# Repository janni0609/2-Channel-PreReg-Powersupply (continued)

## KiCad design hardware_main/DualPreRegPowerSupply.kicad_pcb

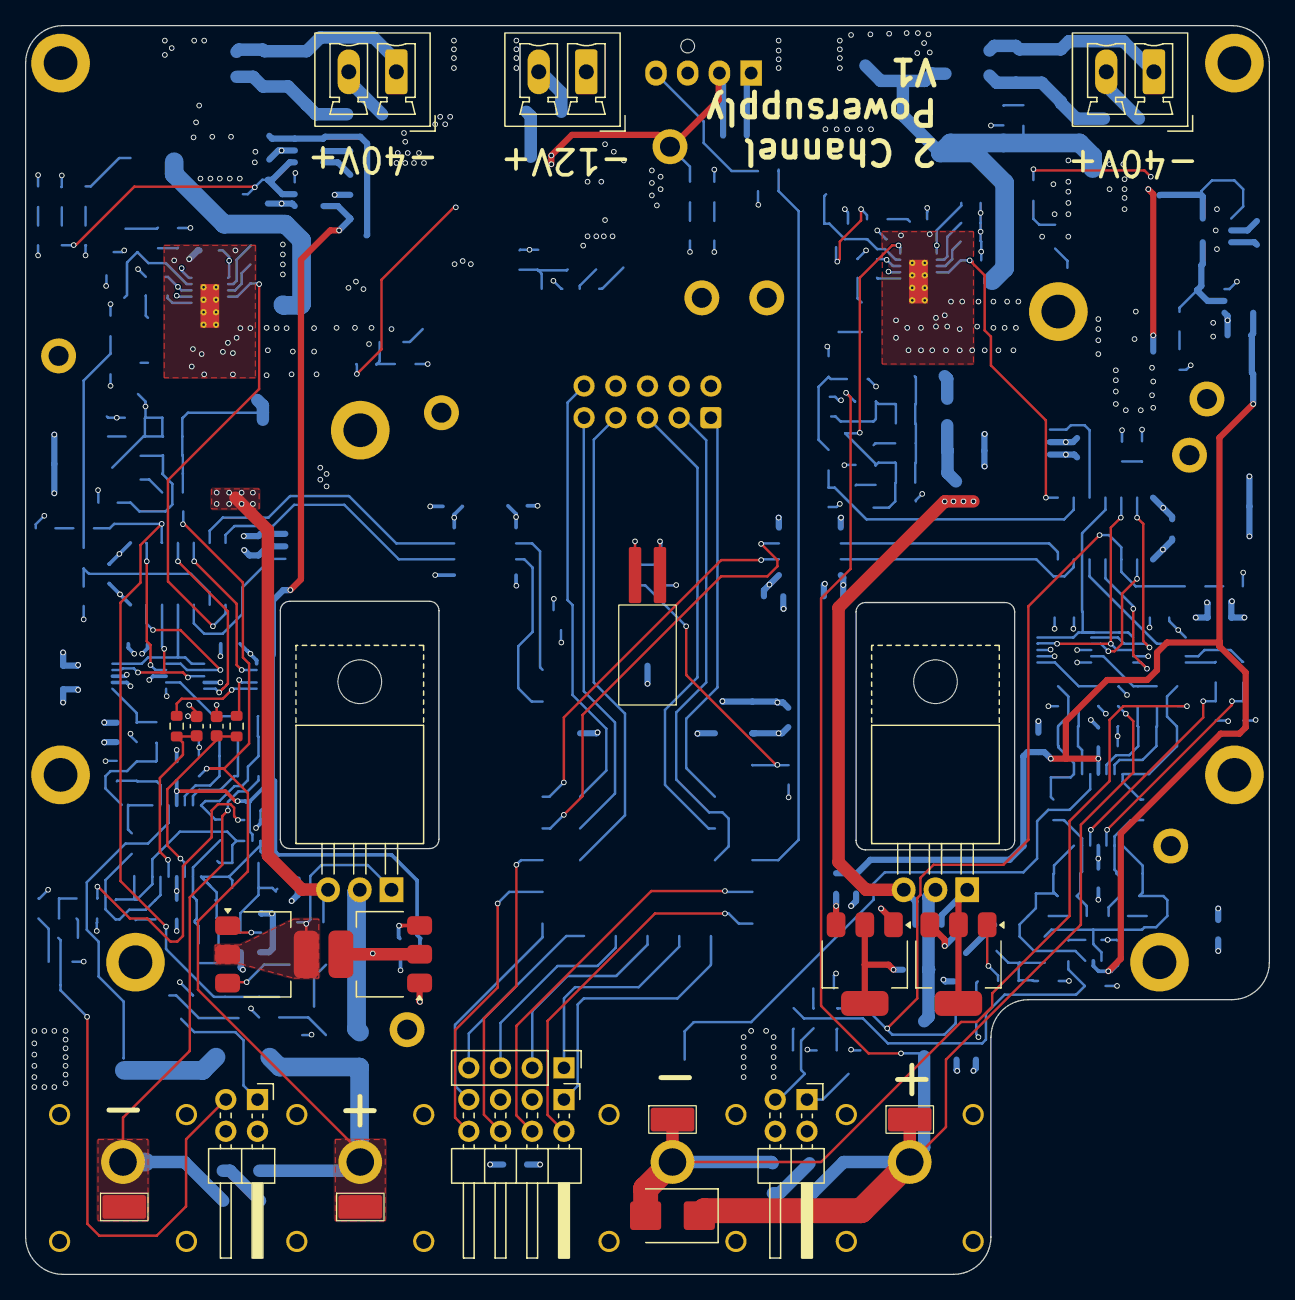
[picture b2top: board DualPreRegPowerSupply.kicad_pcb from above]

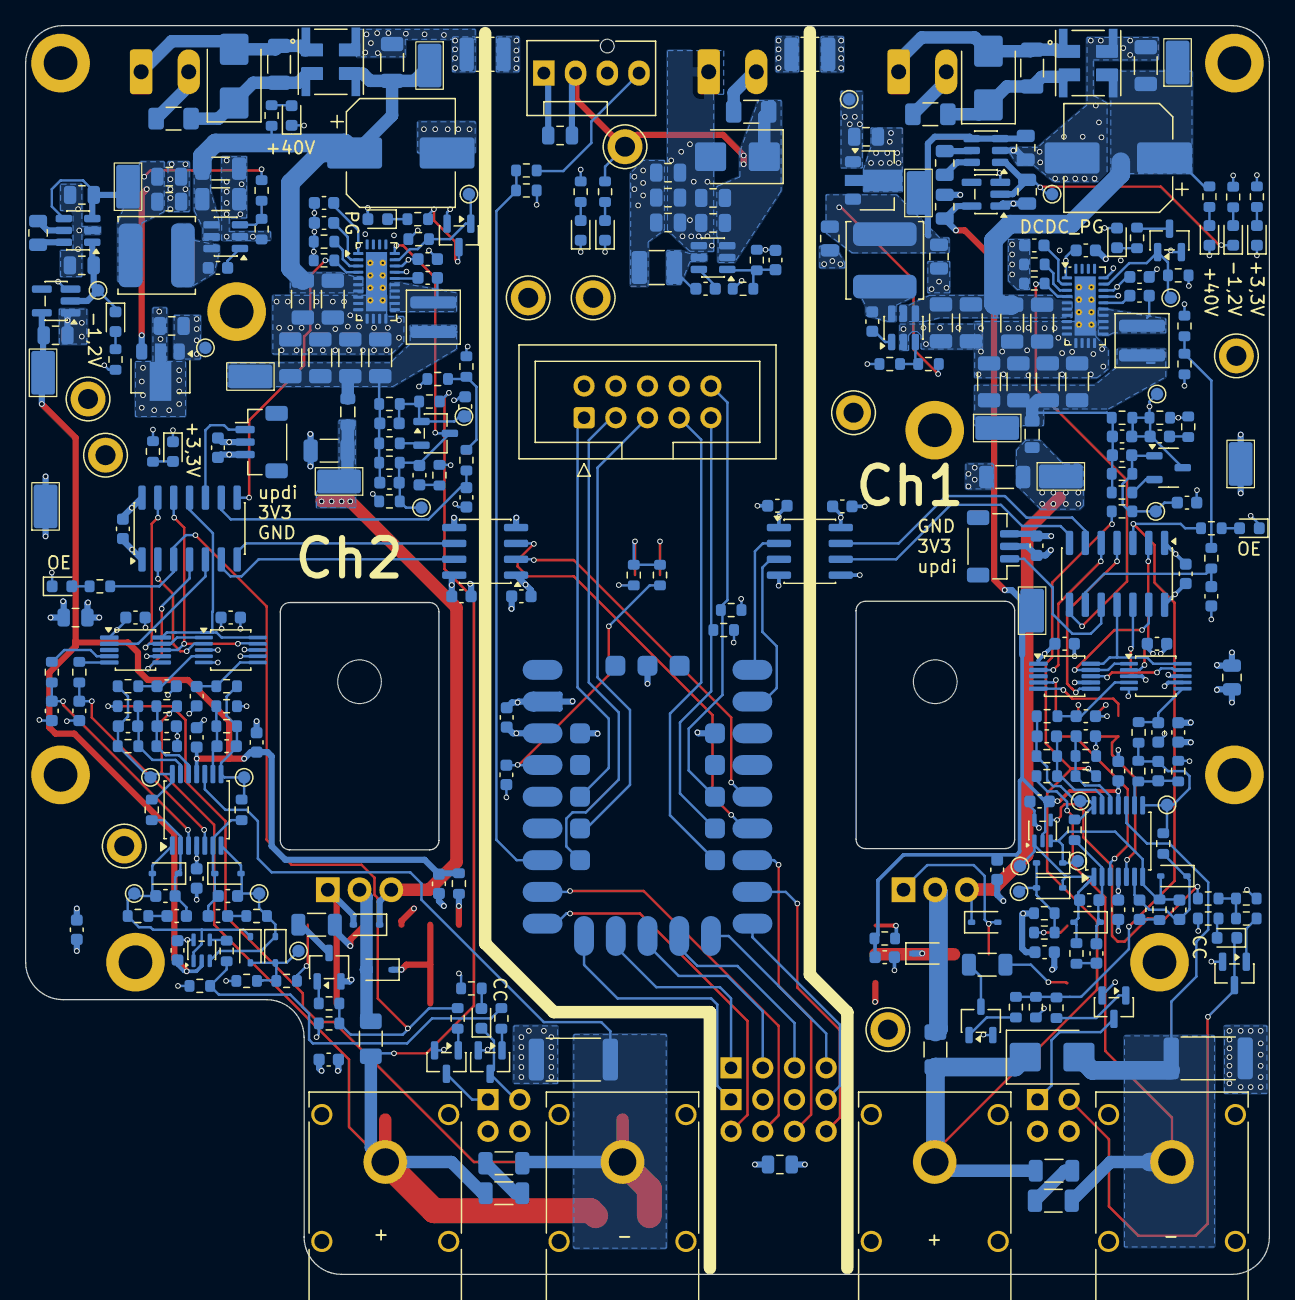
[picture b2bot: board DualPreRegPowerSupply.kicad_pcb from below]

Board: 4 copper layers, 99.6 x 100.0 mm, 379 parts (350 on the bottom side), 195 nets.

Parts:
A401: Waveshare RP2350-Tiny; Waveshare_PR2350_tiny
C101, C102, C105, C107, C120, C135, C136, C140, C141, C143, C145, C201, C309, C405, C501, C502, C509, C511, C512, C513, C601, C603, C1001, C1002: 10u; C_1206_3216Metric
C103, C104, C106, C108, C109, C115, C117, C118, C126, C128, C132, C144, C147, C301, C302, C307, C310, C402, C503, C505, C703, C704, C801, C802, C803, C805, C806, C903, C1003, C1015, C1205, C1301: 100n; C_0603_1608Metric
C110, C122, C123, C203, C504, C507, C804: 1u; C_0603_1608Metric
C111, C303: 47n; C_0603_1608Metric
C112, C304, C807, C1302: 27n; C_0603_1608Metric
C113, C114, C701, C702: 4,7u; C_0603_1608Metric
C119, C137, C506, C510, C908, C1401: opt; C_0603_1608Metric
C121, C130, C134, C305, C306, C308: 10p; C_0603_1608Metric
C124, C131, C905, C906, C907, C1005, C1007: 22u; C_0805_2012Metric
C125, C602: CHV1210N1K0103KXT; C_1210_3225Metric
C127, C139, C142, C146, C202, C404, C808, C901, C902, C1006, C1009, C1010, C1011, C1303: 10u; C_0805_2012Metric
C129, C508: 1n; C_0603_1608Metric
C133, C1008: 1u; C_0805_2012Metric
C138, C604: 100u; CP_Elec_8x10.5
C904, C1004, C1203: 100p; C_0603_1608Metric
C1012, C1013, C1201, C1202: 2,2u; C_0603_1608Metric
C1014, C1204: 22p; C_0603_1608Metric
D101, D601: SMBJ40A; D_SMB
D103, D107, D801, D802: red LED 3V3; LED_0603_1608Metric
D104, D602: green LED 40V; LED_0603_1608Metric
D105, D903, D1001: green LED 3V3; LED_0603_1608Metric
D106, D1002: green LED -5V; LED_0603_1608Metric
D201, D401: SMBJ36A; D_SMB
D901: SMBJ12A; D_SMB
D902: green LED 12V; LED_0603_1608Metric
D904, D1401: green LED PG; LED_0603_1608Metric
D1003, D1004, D1006, D1007, D1008, D1201, D1202, D1204, D1205, D1206: 1N4148WS; D_SOD-323
D1005, D1203: MM3Z4V7T1G; D_SOD-323
F101, F601, F901: 3,5A; Fuse_1206_3216Metric
F102, F301: 3A; Fuse_1206_3216Metric
FL101, FL601: DLW5BTM102TQ2L; L_CommonModeChoke_Murata_DLW5BTMxxxSQ2x_5x5mm
H101, H102, H103, H104, H201, H202, H401, H402: M2,5; MountingHole_2.7mm_M2.5_DIN965_Pad
J101, J601, J901: Power Input; PhoenixContact_MCV_1,5_2-G-3.81_1x02_P3.81mm_Vertical
J102, J801: Conn_01x03_Pin; JST_SH_BM03B-SRSS-TB_1x03-1MP_P1.00mm_Vertical
J103, J802: Conn_02x02_Odd_Even; PinHeader_2x02_P2.54mm_Horizontal
J201, J402: Banana_Red; Banana_Cliff_FCR7350R_S16N-PC_Horizontal
J202, J403: Banana_Black; Banana_Cliff_FCR7350B_S16N-PC_Horizontal
J203: Conn_02x04_Odd_Even; PinHeader_2x04_P2.54mm_Horizontal
J204: Conn_02x05_Odd_Even; IDC-Header_2x05_P2.54mm_Vertical
J205: Conn_01x04_Pin; PinHeader_1x04_P2.54mm_Vertical
L101, L1001: 33u VLS6045EX-330M; L_TDK_VLS6045EX_VLS6045AF
L102, L501: 10u 74438357100; L_Wuerth_MAPI-4030
L201, L401: 1u; L_0805_2012Metric
L901: 6,8u LBC3225T6R8MR; L_1210_3225Metric
M401: Fan_4pin; FanPinHeader_1x04_P2.54mm_Vertical
Q101, Q501: MMBT3906; SOT-23-3
Q102, Q107, Q301, Q304: BCP56; SOT-223
Q103, Q302: BSS138; SOT-23-3
Q104, Q303: TIP125; TO-220-3_Horizontal_TabUp
Q105, Q106, Q801, Q802, Q901, Q1401: BSS138; SOT-23
R101, R102, R103, R109, R113, R120, R201, R202, R203, R204, R205, R301, R302, R310, R501, R801, R802, R808, R906, R1302, R1402: 10k; R_0603_1608Metric
R104, R105, R118, R125, R135, R137, R308, R404, R506, R701, R702, R804, R805: 1k; R_0603_1608Metric
R106, R303: 18k; R_0603_1608Metric
R107, R121, R304, R311: 0; R_0603_1608Metric
R108, R502: 60,4k; R_0603_1608Metric
R110, R122, R503, R505: opt; R_0603_1608Metric
R112, R305: 1,2k; R_0603_1608Metric
R114, R1001: 75k; R_0603_1608Metric
R115, R1002: 16,2k; R_0603_1608Metric
R116, R119, R306, R309: 2,2k 0,1%; R_0603_1608Metric
R117, R307: 3,3k; R_0603_1608Metric
R123, R312: 220; R_0603_1608Metric
R124, R136, R140, R803, R806, R905, R1003, R1401: 2,4k; R_0603_1608Metric
R126, R507: 4,99k; R_0603_1608Metric
R127, R128, R313, R314: 33k 0,1%; R_0603_1608Metric
R129, R315: 150; R_1206_3216Metric
R130, R508, R903: 62k; R_0603_1608Metric
R131, R316: 11k 0,1%; R_0603_1608Metric
R132, R317: 1k 0,1%; R_0603_1608Metric
R133, R509: 100k; R_0603_1608Metric
R134, R601: 38k; R_0603_1608Metric
R138, R318: 100m; R_2512_6332Metric
R139, R901, R904, R1004: ###; R_0603_1608Metric
R141, R319: 200m; R_1206_3216Metric
R142, R320: 47; R_0603_1608Metric
R807, R1301: 12k; R_0603_1608Metric
R902: 196k; R_0603_1608Metric
TH101, TH801: NCU18XH103F60RB; R_0603_1608Metric
TH201: Thermistor_NTC; Flex NTC
TP101, TP301: Vsense; TestPoint_Pad_D1.0mm
TP102, TP302: CV_loop; TestPoint_Pad_D1.0mm
TP103, TP303: CC_loop; TestPoint_Pad_D1.0mm
TP104, TP304: CC/CV; TestPoint_Pad_D1.0mm
TP105, TP305: Isense; TestPoint_Pad_D1.0mm
TP106, TP107, TP110, TP501, TP502, TP503, TP608, TP901, TP1401, TP1506: TestPoint_Alt; TestPoint_Pad_D1.0mm
TP108, TP112, TP201, TP202, TP203, TP401, TP402, TP403, TP505, TP601, TP605, TP606, TP607, TP1503, TP1504, TP1505: TestPoint; SMD Test Point PCWCTE
TP306, TP307, TP308, TP602, TP603, TP604, TP1501, TP1502, TP1507: TestPoint_Alt; TestPoint_Keystone_5005-5009_Compact
U101, U301: TLV4387PWR; TSSOP-14_4.4x5mm_P0.65mm
U102, U801: ISO6721RFBD; SOIC-8_3.9x4.9mm_P1.27mm
U104, U501: LT8612; QFN-28-1EP_3x6mm_P0.5mm_EP1.7x4.75mm_ThermalVias
U105, U302: LMV331; SOT-353_SC-70-5
U106, U802: ATtiny1614-SS; SOIC-14_3.9x8.7mm_P1.27mm
U107, U701: ADS1118IDGS; TSSOP-10_3x3mm_P0.5mm
U108, U702: MCP48FVB22; MSOP-10_3x3mm_P0.5mm
U109, U1002: AP7383; SOT-89-3
U110, U1003: LM2776; SOT-23-6
U111, U1004: XC6901D121MR-G; SC-74A-5_1.55x2.9mm_P0.95mm
U601, U1501: LMR51606; SOT-23-6
U901: AP63200WU; TSOT-23-6

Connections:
+3.3V: A401.30 (3V3), A401.35 (3V3), C106.1, C202.1, C402.1, C801.1, C904.1, C905.1, C906.1, C907.1, J203.3, J204.8, L901.2, R201.2, R203.2, R204.2, R902.1, R904.1, TP307.1 (1_1), U102.1 (VCC1), U801.1 (VCC1)
+3V3Ch1: C301.1, C307.1, C507.1, C703.1, C704.1, C802.1, C803.1, C805.1, C808.1, C1009.1, C1012.1, C1015.1, D904.2 (A), J801.2, J802.2, J802.4, R307.1, R308.1, R801.1, R806.1, R906.1, R1003.1, TP501.1 (1_1), TP602.1 (1_1), TP606.1 (1_1), U301.4 (V+), U302.5 (V+), U501.22 (BIAS), U701.8 (VDD), U702.1 (Vdd), U801.8 (VCC2), U802.1 (VCC), U1002.1 (VO), U1004.3 (CE)
+3V3Ch2: C103.1, C109.1, C117.1, C123.1, C126.1, C128.1, C132.1, C139.1, C144.1, C1201.1, C1205.1, C1303.1, D1401.2 (A), J102.2, J103.2, J103.4, R109.1, R117.1, R118.1, R136.1, R140.1, R1402.1, TP106.1 (1_1), TP1504.1 (1_1), TP1507.1 (1_1), U101.4 (V+), U102.8 (VCC2), U104.22 (BIAS), U105.5 (V+), U106.1 (VCC), U107.8 (VDD), U108.1 (Vdd), U109.1 (VO), U111.3 (CE)
+12V: C404.1, C901.1, C902.1, D901.1 (A1), F901.2, M401.2 (+), R901.1, TP308.1 (1_1), U901.2 (EN), U901.3 (IN)
+40VCh1: C501.1, C502.1, C603.1, C604.1, C1001.1, C1002.1, FL601.3, R601.1, TP601.1 (1_1), U501.5 (Vin), U501.6 (Vin), U501.7 (Vin), U601.4 (EN), U601.5 (VIN)
+40VCh2: C101.1, C102.1, C105.1, C107.1, C135.1, C138.1, FL101.3, R134.1, TP108.1 (1_1), U104.5 (Vin), U104.6 (Vin), U104.7 (Vin), U1501.4 (EN), U1501.5 (VIN)
-1V2Ch1: C302.2, C307.2, C310.2, C1011.2, C1013.2, R320.2, TP607.1 (1_1), U301.11 (V-), U302.2 (V-), U1004.5 (VOUT)
-1V2Ch2: C104.2, C132.2, C146.2, C147.2, C1202.2, R142.2, TP1505.1 (1_1), U101.11 (V-), U105.2 (V-), U111.5 (VOUT)
/Ch1Power1/DAC_ADC/DAC_LAT: U106.4 (PA6), U108.6 (LAT/HVC)
/Ch1Power1/DAC_ADC/Isense: C134.1, R103.1, R105.2, R131.1, TP105.1 (1_1), U101.8
/Ch1Power1/DAC_ADC/Iset: C1302.1, R1302.1, U101.5 (+)
/Ch1Power1/DAC_ADC/SPI_ADC_CS: U106.2 (PA4), U107.2 (~CS)
/Ch1Power1/DAC_ADC/SPI_DAC_CS: U106.5 (PA7), U108.2 (~CS)
/Ch1Power1/DAC_ADC/SPI_MISO: U106.12 (PA2), U107.9 (DOUT/~DRDY), U108.8 (SDO)
/Ch1Power1/DAC_ADC/SPI_MOSI: U106.11 (PA1), U107.10 (DIN), U108.10 (SDI)
/Ch1Power1/DAC_ADC/SPI_SCK: U106.13 (PA3), U107.1 (SCLK), U108.9 (SCK)
/Ch1Power1/DAC_ADC/Vsense: C121.1, R102.1, R104.2, R116.1, TP101.1 (1_1), U101.14
/Ch1Power1/DAC_ADC/Vset: C1301.1, R1301.1, U101.3 (+)
/Ch1Power1/DCDCTracking/BST: C118.1, U104.20 (BST)
/Ch1Power1/DCDCTracking/DCDC_FB: C119.1, C129.1, Q101.3 (C), R122.1, R126.2, TP107.1 (1_1), U104.24 (FB)
/Ch1Power1/DCDCTracking/Enable: R101.2, U104.4 (EN/UV), U106.8 (PB1)
/Ch1Power1/DCDCTracking/PG: Q1401.1 (G), R1402.2, TP1401.1 (1_1), U104.23 (PG)
/Ch1Power1/DCDCTracking/SW: C118.2, L102.1, U104.15 (SW), U104.16 (SW), U104.17 (SW), U104.18 (SW), U104.19 (SW)
/Ch1Power1/DCDCTracking/SW_OUT: C129.2, C136.1, C137.1, C140.1, C141.1, C143.1, L102.2, L401.1, R122.2, R125.2, R130.2, TP112.1 (1_1)
/Ch1Power1/Input/Input+: F101.1, J101.2
/Ch1Power1/Input/Input-: C120.2, D101.2 (A2), FL101.1, J101.1
/Ch1Power1/Input/Input_Fused+: C120.1, D101.1 (A1), F101.2, FL101.2
/Ch1Power1/Linear_PostReg/Base: Q102.1 (B), R121.2
/Ch1Power1/Linear_PostReg/Base_drive: D1203.2 (A), Q102.2 (C), Q102.4 (C), Q104.1 (B)
/Ch1Power1/Linear_PostReg/CC_loop: C1203.2, D1201.2 (A), D1205.1 (K), R107.2, TP103.1 (1_1), U101.7, U105.3 (-)
/Ch1Power1/Linear_PostReg/CC/CV_loop: D1205.2 (A), D1206.2 (A), R118.2, R121.1, TP104.1 (1_1)
/Ch1Power1/Linear_PostReg/CC/~CV: R112.2, R117.2, R137.1
/Ch1Power1/Linear_PostReg/CV_loop: C1204.2, D1202.2 (A), D1206.1 (K), R106.2, TP102.1 (1_1), U101.1, U105.1 (+)
/Ch1Power1/Linear_PostReg/OE: R120.2, R123.2, R124.1, R135.1, U106.3 (PA5)
/Ch1Power1/Linear_PostReg/OUT+: D401.1 (A1), F102.2, J402.1 (Pin_1_1), R127.2, R133.2, R141.1, TP402.1 (1_1)
/Ch1Power1/Linear_PostReg/OUT-: C145.2, D401.2 (A2), J403.1 (Pin_1_1), R128.2, R138.1, TP403.1 (1_1), U101.10 (+)
/Ch1Power1/Linear_PostReg/PreReg: C405.1, D1203.1 (K), L401.2, Q104.3 (E), TP401.1 (1_1)
/Ch1Power1/Linear_PostReg/preFuseOut+: D1204.2 (A), F102.1, Q104.2 (C)
/Ch1Power1/MCU/NTC1: C122.1, R113.2, U106.9 (PB0)
/Ch1Power1/MCU/Rx: U102.7 (OUTA), U106.6 (PB3)
/Ch1Power1/MCU/Tx: U102.6 (INB), U106.7 (PB2)
/Ch1Power1/MCU/UPDI: J102.1, U106.10 (~RESET/PA0)
/Ch1Power1/MCU/~LED_CC: D107.1 (K), J103.3, Q106.3 (D)
/Ch1Power1/MCU/~LED_Enable: J103.1, Q105.3 (D)
/Ch1Power1/Power/5V: C124.1, C127.1, C131.1, L101.2, R114.1, TP1503.1 (1_1), U109.3 (VI), U110.3 (VIN), U110.4 (EN)
/Ch1Power1/Power/SW: C115.2, L101.1, U1501.6 (SW)
/Ch1Power1/Rx_Ctr: A401.5 (GPIO5), U102.3 (OUTB)
/Ch1Power1/Tx_Ctr: A401.4 (GPIO4), U102.2 (INA)
/Ch1Power/DAC_ADC/DAC_LAT: U702.6 (LAT/HVC), U802.4 (PA6)
/Ch1Power/DAC_ADC/Isense: C308.1, R302.1, R316.1, R702.2, TP305.1 (1_1), U301.8
/Ch1Power/DAC_ADC/Iset: C807.1, R808.1, U301.5 (+)
/Ch1Power/DAC_ADC/SPI_ADC_CS: U701.2 (~CS), U802.2 (PA4)
/Ch1Power/DAC_ADC/SPI_DAC_CS: U702.2 (~CS), U802.5 (PA7)
/Ch1Power/DAC_ADC/SPI_MISO: U701.9 (DOUT/~DRDY), U702.8 (SDO), U802.12 (PA2)
/Ch1Power/DAC_ADC/SPI_MOSI: U701.10 (DIN), U702.10 (SDI), U802.11 (PA1)
/Ch1Power/DAC_ADC/SPI_SCK: U701.1 (SCLK), U702.9 (SCK), U802.13 (PA3)
/Ch1Power/DAC_ADC/Vsense: C305.1, R301.1, R306.1, R701.2, TP301.1 (1_1), U301.14
/Ch1Power/DAC_ADC/Vset: C806.1, R807.1, U301.3 (+)
/Ch1Power/DCDCTracking/BST: C505.1, U501.20 (BST)
/Ch1Power/DCDCTracking/DCDC_FB: C506.1, C508.1, Q501.3 (C), R505.1, R507.2, TP502.1 (1_1), U501.24 (FB)
/Ch1Power/DCDCTracking/Enable: R501.2, U501.4 (EN/UV), U802.8 (PB1)
/Ch1Power/DCDCTracking/PG: Q901.1 (G), R906.2, TP901.1 (1_1), U501.23 (PG)
/Ch1Power/DCDCTracking/SW: C505.2, L501.1, U501.15 (SW), U501.16 (SW), U501.17 (SW), U501.18 (SW), U501.19 (SW)
/Ch1Power/DCDCTracking/SW_OUT: C508.2, C509.1, C510.1, C511.1, C512.1, C513.1, L201.1, L501.2, R505.2, R506.2, R508.2, TP505.1 (1_1)
/Ch1Power/Input/Input+: F601.1, J601.2
/Ch1Power/Input/Input-: C601.2, D601.2 (A2), FL601.1, J601.1
/Ch1Power/Input/Input_Fused+: C601.1, D601.1 (A1), F601.2, FL601.2
/Ch1Power/Linear_PostReg/Base: Q301.1 (B), R311.2
/Ch1Power/Linear_PostReg/Base_drive: D1005.2 (A), Q301.2 (C), Q301.4 (C), Q303.1 (B)
/Ch1Power/Linear_PostReg/CC_loop: C1004.2, D1003.2 (A), D1007.1 (K), R304.2, TP303.1 (1_1), U301.7, U302.3 (-)
/Ch1Power/Linear_PostReg/CC/CV_loop: D1007.2 (A), D1008.2 (A), R308.2, R311.1, TP304.1 (1_1)
/Ch1Power/Linear_PostReg/CC/~CV: R305.2, R307.2, R805.1
/Ch1Power/Linear_PostReg/CV_loop: C1014.2, D1004.2 (A), D1008.1 (K), R303.2, TP302.1 (1_1), U301.1, U302.1 (+)
/Ch1Power/Linear_PostReg/OE: R310.2, R312.2, R803.1, R804.1, U802.3 (PA5)
/Ch1Power/Linear_PostReg/OUT+: D201.1 (A1), F301.2, J201.1 (Pin_1_1), R313.2, R319.1, R509.2, TP202.1 (1_1)
/Ch1Power/Linear_PostReg/OUT-: C309.2, D201.2 (A2), J202.1 (Pin_1_1), R314.2, R318.1, TP203.1 (1_1), U301.10 (+)
/Ch1Power/Linear_PostReg/PreReg: C201.1, D1005.1 (K), L201.2, Q303.3 (E), TP201.1 (1_1)
/Ch1Power/Linear_PostReg/preFuseOut+: D1006.2 (A), F301.1, Q303.2 (C)
/Ch1Power/MCU/NTC1: C804.1, R802.2, U802.9 (PB0)
/Ch1Power/MCU/Rx: U801.7 (OUTA), U802.6 (PB3)
/Ch1Power/MCU/Tx: U801.6 (INB), U802.7 (PB2)
/Ch1Power/MCU/UPDI: J801.1, U802.10 (~RESET/PA0)
/Ch1Power/MCU/~LED_CC: D802.1 (K), J802.3, Q802.3 (D)
/Ch1Power/MCU/~LED_Enable: J802.1, Q801.3 (D)
/Ch1Power/Power/5V: C1005.1, C1006.1, C1007.1, L1001.2, R1001.1, TP605.1 (1_1), U1002.3 (VI), U1003.3 (VIN), U1003.4 (EN)
/Ch1Power/Power/SW: C1003.2, L1001.1, U601.6 (SW)
/Ch1Power/Rx_Ctr: A401.1 (GPIO1), U801.3 (OUTB)
/Ch1Power/Tx_Ctr: A401.0 (GPIO0), U801.2 (INA)
/Control/CS: A401.13 (GPIO13), J203.1
/Control/DC: A401.12 (GPIO12), J205.1
/Control/Digi_Power/SW: C903.2, L901.1, U901.5 (SW)
/Control/FanPWM: A401.26 (GPIO26_ADC0), R202.2, R404.1
/Control/RESET: A401.9 (GPIO9), J205.4
/Control/ROT_A: A401.14 (GPIO14), J203.2
/Control/ROT_B: A401.15 (GPIO15), J203.4
/Control/SCK: A401.10 (GPIO10), J205.3
/Control/SCL: A401.7 (GPIO7), J203.8
/Control/SDA: A401.6 (GPIO6), J203.6
/Control/SDI(MOSI): A401.11 (GPIO11), J205.2
/Control/W5500_CS: A401.17 (GPIO17), J204.1
/Control/W5500_INT: A401.22 (GPIO22), J204.10, R201.1
/Control/W5500_MISO: A401.20 (GPIO20), J204.7
/Control/W5500_MOSI: A401.19 (GPIO19), J204.3
/Control/W5500_RST: A401.21 (GPIO21), J204.9, R203.1
/Control/W5500_SCLK: A401.18 (GPIO18), J204.5
/Control/~INT: A401.8 (GPIO8), J203.7
GNDD: A401.31 (GND), A401.34 (GND), A401.D2 (GND), C106.2, C125.1, C202.2, C203.2, C402.2, C404.2, C602.1, C801.2, C901.2, C902.2, C905.2, C906.2, C907.2, D901.2 (A2), D902.1 (K), D903.1 (K), J203.5, J204.2, J204.4, J204.6, J901.1, M401.1 (-), R202.1, R903.2, TH201.2, TP306.1 (1_1), U102.4 (GND1), U801.4 (GND1), U901.4 (GND)
GND_Ch1: C201.2, C301.2, C302.1, C306.1, C310.1, C501.2, C502.2, C503.2, C504.2, C507.2, C509.2, C511.2, C512.2, C513.2, C602.2, C603.2, C604.2, C701.2, C702.2, C703.2, C704.2, C802.2, C803.2, C804.2, C805.2, C806.2, C807.2, C808.2, C908.2, C1001.2, C1002.2, C1005.2, C1006.2, C1007.2, C1009.2, C1010.2, C1011.1, C1012.2, C1013.1, C1015.2, D602.1 (K), D801.1 (K), D1001.1 (K), FL601.4, J801.3, Q302.2 (S), Q304.1 (B), Q801.2 (S), Q802.2 (S), Q901.2 (S), R309.2, R310.1, R317.2, R318.2, R501.1, R502.2, R503.2, R507.1, R1002.2, R1004.1, TH801.2, TP603.1 (1_1), TP604.1 (1_1), U501.8 (PGND), U501.9 (PGND), U501.10 (PGND), U501.11 (GND), U501.12 (GND), U501.13 (GND), U501.14 (GND), U501.29 (GND), U601.2 (GND), U701.3 (GND), U701.5 (AIN1), U701.7 (AIN3), U702.7 (Vss), U801.5 (GND2), U802.14 (GND), U1002.2 (GND), U1003.2 (GND), U1004.1 (GND)
GND_Ch2: C101.2, C102.2, C103.2, C104.1, C105.2, C107.2, C108.2, C109.2, C110.2, C113.2, C114.2, C117.2, C122.2, C123.2, C124.2, C125.2, C126.2, C127.2, C128.2, C130.1, C131.2, C135.2, C136.2, C138.2, C139.2, C140.2, C141.2, C142.2, C143.2, C144.2, C146.1, C147.1, C405.2, C1201.2, C1202.1, C1205.2, C1301.2, C1302.2, C1303.2, C1401.2, D103.1 (K), D104.1 (K), D105.1 (K), FL101.4, J102.3, Q103.2 (S), Q105.2 (S), Q106.2 (S), Q107.1 (B), Q1401.2 (S), R101.1, R108.2, R110.2, R115.2, R119.2, R120.1, R126.1, R132.2, R138.2, R139.1, TH101.2, TP1501.1 (1_1), TP1502.1 (1_1), U102.5 (GND2), U104.8 (PGND), U104.9 (PGND), U104.10 (PGND), U104.11 (GND), U104.12 (GND), U104.13 (GND), U104.14 (GND), U104.29 (GND), U106.14 (GND), U107.3 (GND), U107.5 (AIN1), U107.7 (AIN3), U108.7 (Vss), U109.2 (GND), U110.2 (GND), U111.1 (GND), U1501.2 (GND)
unnamed: A401.29 (GPIO29_ADC3), C203.1, R205.2
unnamed: C111.2, R106.1
unnamed: C112.2, R107.1
unnamed: C119.2, R110.1
unnamed: C145.1, R141.2
unnamed: C303.2, R303.1
unnamed: C304.2, R304.1
unnamed: C309.1, R319.2
unnamed: C506.2, R503.1
unnamed: D103.2 (A), R124.2
unnamed: D104.2 (A), R134.2
unnamed: D105.2 (A), R136.2
unnamed: D106.2 (A), R139.2
unnamed: C142.1, D106.1 (K), TP1506.1 (1_1), U110.1 (VOUT), U111.2 (VIN)
unnamed: D107.2 (A), R140.2
unnamed: D602.2 (A), R601.2
unnamed: D801.2 (A), R803.2
unnamed: D802.2 (A), R806.2
unnamed: D902.2 (A), R901.2
unnamed: D903.2 (A), R904.2
unnamed: D904.1 (K), R905.1
unnamed: D1001.2 (A), R1003.2
unnamed: D1002.2 (A), R1004.2
unnamed: C1010.1, D1002.1 (K), TP608.1 (1_1), U1003.1 (VOUT), U1004.2 (VIN)
unnamed: C304.1, C1004.1, D1003.1 (K), R302.2, U301.6 (-)
unnamed: C303.1, C1014.1, D1004.1 (K), R301.2, U301.2 (-)
unnamed: D1006.1 (K), Q304.2 (C), Q304.4 (C)
unnamed: C112.1, C1203.1, D1201.1 (K), R103.2, U101.6 (-)
unnamed: C111.1, C1204.1, D1202.1 (K), R102.2, U101.2 (-)
unnamed: D1204.1 (K), Q107.2 (C), Q107.4 (C)
unnamed: D1401.1 (K), R1401.1
unnamed: F901.1, J901.2
unnamed: M401.4 (PWM), R404.2
unnamed: C137.2, C1401.1, Q101.1 (B), R130.1, R133.1, TP110.1 (1_1)
unnamed: Q101.2 (E), R125.1
unnamed: Q102.3 (E), R129.1
unnamed: Q103.3 (D), R129.2
unnamed: Q103.1 (G), R123.1
unnamed: Q105.1 (G), R135.2
unnamed: Q106.1 (G), R137.2
unnamed: Q107.3 (E), R142.1
unnamed: Q301.3 (E), R315.1
unnamed: Q302.3 (D), R315.2
unnamed: Q302.1 (G), R312.1
unnamed: Q304.3 (E), R320.1
unnamed: C510.2, C908.1, Q501.1 (B), R508.1, R509.1, TP503.1 (1_1)
unnamed: Q501.2 (E), R506.1
unnamed: Q801.1 (G), R804.2
unnamed: Q802.1 (G), R805.2
unnamed: Q901.3 (D), R905.2
unnamed: Q1401.3 (D), R1401.2
unnamed: R109.2, R113.1, TH101.1
unnamed: R112.1, U105.4
unnamed: R204.1, R205.1, TH201.1
unnamed: R305.1, U302.4
unnamed: R801.2, R802.1, TH801.1
unnamed: C134.2, R131.2, R132.1, U101.9 (-)
unnamed: C130.2, R119.1, R127.1, U101.12 (+)
unnamed: C121.2, R116.2, R128.1, U101.13 (-)
unnamed: C110.1, U104.1 (SYNC), U104.21 (INT_Vcc)
unnamed: R108.1, U104.3 (RT)
unnamed: C108.1, U104.2 (TR/SS)
unnamed: C113.1, R104.1, U107.4 (AIN0)
unnamed: C114.1, R105.1, U107.6 (AIN2)
unnamed: R1301.2, U108.4 (VA)
unnamed: R1302.2, U108.5 (VB)
unnamed: C133.1, U110.5 (C1+)
unnamed: C133.2, U110.6 (C1-)
unnamed: C308.2, R316.2, R317.1, U301.9 (-)
unnamed: C306.2, R309.1, R313.1, U301.12 (+)
unnamed: C305.2, R306.2, R314.1, U301.13 (-)
unnamed: C504.1, U501.1 (SYNC), U501.21 (INT_Vcc)
unnamed: R502.1, U501.3 (RT)
unnamed: C503.1, U501.2 (TR/SS)
unnamed: C1003.1, U601.1 (CB)
unnamed: R1001.2, R1002.1, U601.3 (FB)
unnamed: C701.1, R701.1, U701.4 (AIN0)
unnamed: C702.1, R702.1, U701.6 (AIN2)
unnamed: R807.2, U702.4 (VA)
unnamed: R808.2, U702.5 (VB)
unnamed: C903.1, U901.6 (BST)
unnamed: C904.2, R902.2, R903.1, U901.1 (FB)
unnamed: C1008.1, U1003.5 (C1+)
unnamed: C1008.2, U1003.6 (C1-)
unnamed: C115.1, U1501.1 (CB)
unnamed: R114.2, R115.1, U1501.3 (FB)

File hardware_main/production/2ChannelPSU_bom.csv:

Designator,Footprint,Quantity,Value,LCSC Part #
A401,Waveshare_PR2350_tiny,1,Waveshare RP2350-Tiny,
"C1001, C1002, C101, C102, C105, C107, C120, C135, C136, C140, C141, C143, C145, C201, C309, C405, C501, C502, C509, C511, C512, C513, C601, C603",1206,24,10u,
"C1003, C103, C104, C106, C108, C109, C115, C117, C118, C126, C128, C132, C144, C147, C301, C302, C307, C310, C402, C503, C505, C703, C704, C801, C802, C803, C805, C903",0603,28,100n,
"C1004, C1203, C904",0603,3,100p,
"C1005, C1007, C124, C131, C905, C906, C907",0805,7,22u,
"C1006, C1009, C1010, C1011, C127, C139, C142, C146, C202, C404, C901, C902",0805,12,10u,
"C1008, C133, L201, L401",0805,4,1u,
"C1012, C1013, C1201, C1202",0603,4,"2,2u",
"C1014, C1204",0603,2,22p,
"C110, C122, C123, C203, C504, C507, C804",0603,7,1u,
"C111, C303",0603,2,47n,
"C112, C304",0603,2,27n,
"C113, C114, C1301, C1302, C701, C702, C806, C807",0603,8,"4,7u",
"C119, C137, C1401, C506, C510, C908, R110, R122, R503, R505",0603,10,opt,
"C121, C130, C134, C305, C306, C308",0603,6,10p,
"C125, C602",1210,2,CHV1210N1K0103KXT,
"C129, C508",0603,2,1n,
"C138, C604",CP_Elec_8x10.5,2,100u,
"D1001, D105, D903",0603,3,green LED 3V3,
"D1002, D106",0603,2,green LED -5V,
"D1003, D1004, D1006, D1007, D1008, D1201, D1202, D1204, D1205, D1206",D_SOD-323,10,1N4148WS,
"D1005, D1203",D_SOD-323,2,MM3Z4V7T1G,
"D101, D601",D_SMB,2,SMBJ40A,
"D103, D107, D801, D802",0603,4,red LED 3V3,
"D104, D602",0603,2,green LED 40V,
"D1401, D904",0603,2,green LED PG,
"D201, D401",D_SMB,2,SMBJ36A,
D901,D_SMB,1,SMBJ12A,
D902,0603,1,green LED 12V,
"F101, F601, F901",1206,3,"3,5A",
"F102, F301",1206,2,Fuse,
"FL101, FL601",ACM4520_TDK,2,ACM4520-901-2P-T000,
"J101, J601, J901","PhoenixContact_MCV_1,5_2-G-3.81_1x02_P3.81mm_Vertical",3,Power Input,
"J102, J801",JST_SH_BM03B-SRSS-TB_1x03-1MP_P1.00mm_Vertical,2,Conn_01x03_Pin,
"J103, J802",PinHeader_2x02_P2.54mm_Horizontal,2,Conn_02x02_Odd_Even,
"J201, J402",Banana_Cliff_FCR7350R_S16N-PC_Horizontal,2,Banana_Red,
"J202, J403",Banana_Cliff_FCR7350B_S16N-PC_Horizontal,2,Banana_Black,
J203,PinHeader_2x04_P2.54mm_Horizontal,1,Conn_02x04_Odd_Even,
J204,IDC-Header_2x05_P2.54mm_Vertical,1,Conn_02x05_Odd_Even,
J205,PinHeader_1x04_P2.54mm_Vertical,1,Conn_01x04_Pin,
"L1001, L101",L_TDK_VLS6045EX_VLS6045AF,2,33u VLS6045EX-330M,
"L102, L501",L_Wuerth_MAPI-4030,2,10u 74438357100,
L901,1210,1,"6,8u LBC3225T6R8MR",
M401,FanPinHeader_1x04_P2.54mm_Vertical,1,Fan_4pin,
"Q101, Q501",SOT-23-3,2,MMBT3906,
"Q102, Q107, Q301, Q304",SOT-223,4,BCP56,
"Q103, Q302",SOT-23-3,2,BSS138,
"Q104, Q303",TO-220-3_Horizontal_TabUp,2,TIP125,
"Q105, Q106, Q1401, Q801, Q802, Q901",SOT-23,6,BSS138,
"R1001, R114",0603,2,75k,
"R1002, R115",0603,2,"16,2k",
"R1003, R124, R136, R140, R1401, R803, R806, R905",0603,8,"2,4k",
"R1004, R139, R901, R904",0603,4,###,
"R101, R102, R103, R109, R113, R120, R1402, R201, R202, R203, R204, R205, R301, R302, R310, R501, R801, R802, R906",0603,19,10k,
"R104, R105, R118, R125, R1301, R1302, R135, R137, R308, R404, R506, R701, R702, R804, R805, R807, R808",0603,17,1k,
"R106, R303",0603,2,18k,
"R107, R121, R304, R311",0603,4,0,
"R108, R502",0603,2,"60,4k",
"R112, R305",0603,2,"1,2k",
"R116, R119, R306, R309",0603,4,"2,2k 0,1%",
"R117, R307",0603,2,"3,3k",
"R123, R312",0603,2,220,
"R126, R507",0603,2,"4,99k",
"R127, R128, R313, R314",0603,4,"33k 0,1%",
"R129, R315",1206,2,150,
"R130, R508, R903",0603,3,62k,
"R131, R316",0603,2,"11k 0,1%",
"R132, R317",0603,2,"1k 0,1%",
"R133, R509",0603,2,100k,
"R134, R601",0603,2,38k,
"R138, R318",2512,2,100m,
"R141, R319",1206,2,200m,
"R142, R320",0603,2,47,
R902,0603,1,196k,
"TH101, TH801",0603,2,NCU18XH103F60RB,
TH201,Flex NTC,1,Thermistor_NTC,
"TP101, TP301",TestPoint_Pad_D1.0mm,2,Vsense,
"TP102, TP302",TestPoint_Pad_D1.0mm,2,CV_loop,
"TP103, TP303",TestPoint_Pad_D1.0mm,2,CC_loop,
"TP104, TP304",TestPoint_Pad_D1.0mm,2,CC/CV,
"TP105, TP305",TestPoint_Pad_D1.0mm,2,Isense,
"TP106, TP107, TP110, TP1401, TP1506, TP501, TP502, TP503, TP608, TP901",TestPoint_Pad_D1.0mm,10,TestPoint_Alt,
"TP108, TP112, TP1503, TP1504, TP1505, TP201, TP202, TP203, TP401, TP402, TP403, TP505, TP601, TP605, TP606, TP607",SMD Test Point PCWCTE,16,TestPoint,
"TP1501, TP1502, TP1507, TP306, TP307, TP308, TP602, TP603, TP604",TestPoint_Keystone_5005-5009_Compact,9,TestPoint_Alt,
"U1002, U109",SOT-89-3,2,AP7383,
"U1003, U110",SOT-23-6,2,LM2776,
"U1004, U111",SC-74A-5_1.55x2.9mm_P0.95mm,2,XC6901D121MR-G,
"U101, U301",TSSOP-14_4.4x5mm_P0.65mm,2,TLV4387PWR,
"U102, U801",SOIC-8_3.9x4.9mm_P1.27mm,2,ISO6721RFBD,
"U104, U501",QFN-28-1EP_3x6mm_P0.5mm_EP1.7x4.75mm_ThermalVias,2,LT8612,
"U105, U302",SOT-353_SC-70-5,2,LMV331,
"U106, U802",SOIC-14_3.9x8.7mm_P1.27mm,2,ATtiny1614-SS,
"U107, U701",TSSOP-10_3x3mm_P0.5mm,2,ADS1118IDGS,
"U108, U702",MSOP-10_3x3mm_P0.5mm,2,MCP48FVB22,
"U1501, U601",SOT-23-6,2,LMR51606,
U901,TSOT-23-6,1,AP63200WU,

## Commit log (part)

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2026-06-09 test commit
2026-06-09 test commit 2
2026-06-10 changed pass element drive
2026-06-12 Add plan document for electronic parts library project
2026-06-12 Simplify plan: CSV import via Claude app instead of Anthropic API
2026-06-13 added Ch2 and removed global power flags
2026-06-15 channel 2
2026-06-15 routing
2026-06-16 added loop calc
2026-06-17 added plot function
2026-06-18 add adc and dac estimate
2026-06-18 moove files and add firmware folder
2026-06-19 add diodes for clamping
2026-06-22 added front PCB to repo
2026-06-23 added readme
2026-06-23 cleanup not used schematics
2026-06-23 cleanup
2026-06-25 add first firmware for the channel
